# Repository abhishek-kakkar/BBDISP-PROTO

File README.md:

This is a display cape for the BeagleBone Black using a readily available tablet screen and touch panel.

Visit [this page](https://hackaday.io/project/4410-yet-another-beaglebone-displaycaptouch-cape) for more information.

© 2015 Kumar Abhishek.

Licensed under the CERN Open Hardware License.

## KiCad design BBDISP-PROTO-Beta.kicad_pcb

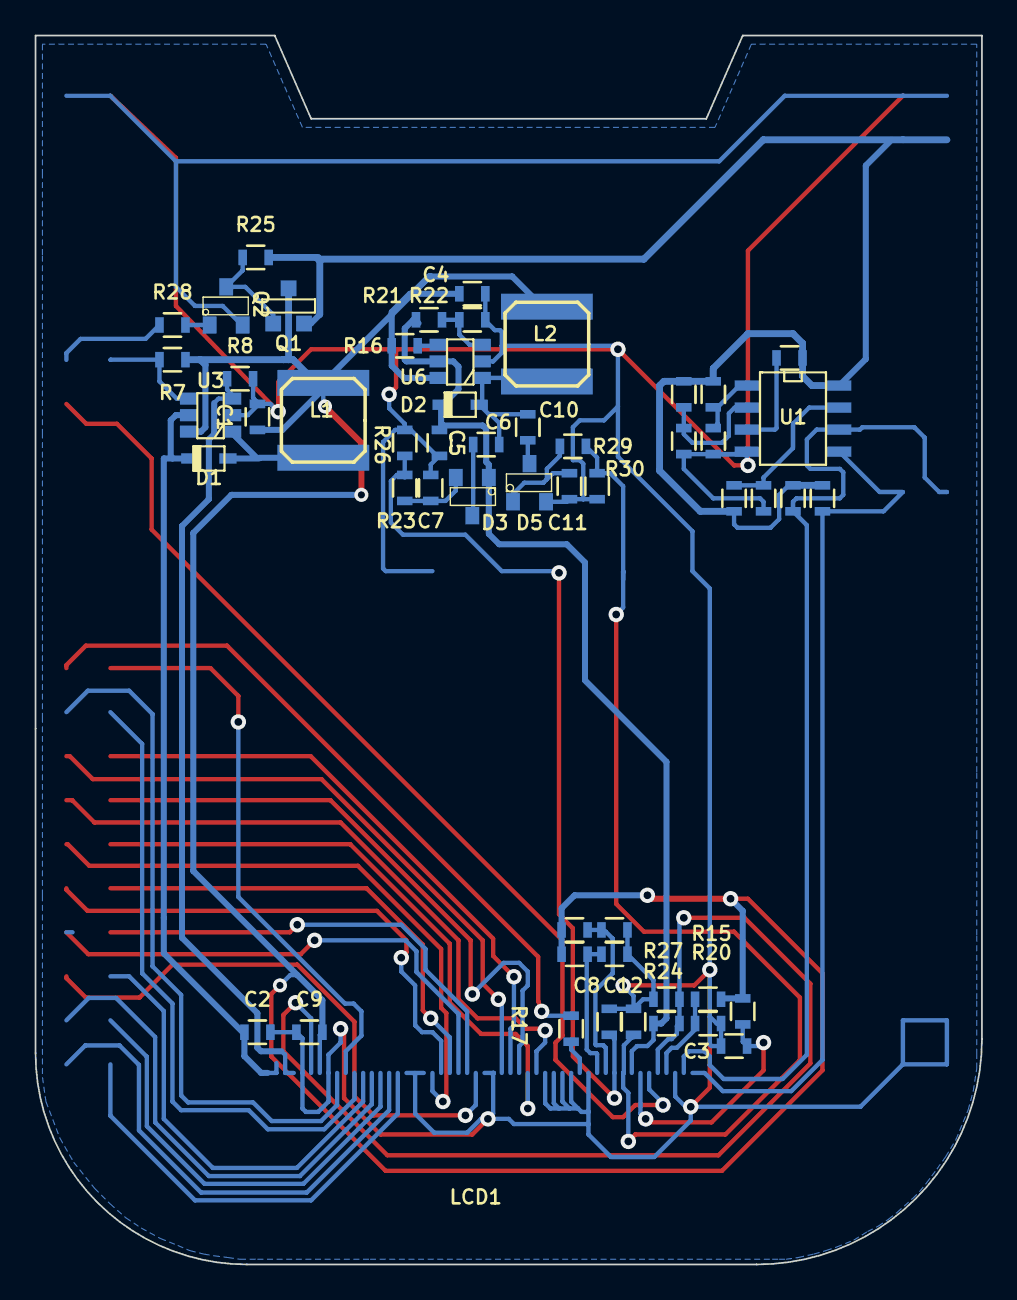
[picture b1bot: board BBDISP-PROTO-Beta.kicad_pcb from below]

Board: 2 copper layers, 54.6 x 70.9 mm, 54 parts (54 on the bottom side), 30 nets.

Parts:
C1, C2, C4, C5: 224; R_0603
C3, C6, C7, C8, C9, C10, C11, C12: 104; R_0603
D1, D2: DIODESCH; sod323
D3, D5: BAT54S; SOT-23_Inv
L1, L2: 22uH; SELF-WE-TPC_M
LCD1: Generic_7; df12a(3.0)-50ds-0.5v
Q1: AO3401; SOT-23-GDS
Q2: BC847; SOT-23
R1, R2: 4K7; R_0603
R3, R4, R5, R6, R7, R9, R10, R11, R12, R16: 10K; R_0603
R8, R13, R14, R15, R17, R18, R19, R20, R21, R22, R24, R27: TBD; R_0603
R23, R29: 1K5; R_0603
R25, R28: 100K; R_0603
R26, R30: 47K; R_0603
U1: AT24CS64-SSHM; SOIC-8-W
U3, U6: SY7201ABC; SOT-23-6

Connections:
+3V3: Q1.S, R1.2, R2.2, R3.2, R4.2, R5.2, R6.2, R25.2, U1.8
+3V3_B: C1.1, C4.1, C9.2, L1.1, L2.1, Q1.D, R7.1, R12.2, R13.1, R14.1, R15.1, R16.1, U3.6, U6.6
/AVDD: C5.1, D2.2, D3.1, R21.1, R24.1, U6.5
/BL_PWM: R7.2, U3.4
/I2C2_SCL: R1.1, U1.6
/I2C2_SDA: R2.1, U1.5
/LCD_DITHB: R15.2, R20.1
/LCD_LR: R13.2, R18.1
/LCD_UD: R14.2, R19.1
/SW1: D1.1, L1.2, U3.1
/SW2: C6.2, C10.2, D2.1, L2.2, U6.1
/VCOM: R24.2, R27.1
/VGH: C8.2, R23.1, R26.2
/VGL: C12.2, R29.1, R30.2
/VLED: C2.1, D1.2, U3.5
GND: C1.2, C2.2, C3.1, C4.2, C5.2, C7.1, C8.1, C9.1, C11.1, C12.1, D5.3, Q2.2, R8.2, R9.1, R10.1, R11.1, R18.2, R19.2, R20.2, R22.2, R26.1, R27.2, R30.1, U1.4, U3.2, U6.2
unnamed: C3.2, R12.1
unnamed: C6.1, D3.2
unnamed: C7.2, D3.3, R23.2
unnamed: C10.1, D5.2
unnamed: C11.2, D5.1, R29.2
unnamed: R8.1, U3.3
unnamed: Q1.G, Q2.3, R25.1
unnamed: Q2.1, R28.2
unnamed: R3.1, R9.2, U1.7
unnamed: R4.1, U1.3
unnamed: R5.1, R10.2, U1.2
unnamed: R6.1, R11.2, U1.1
unnamed: R16.2, U6.4
unnamed: R21.2, R22.1, U6.3

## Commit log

2015-05-27 Add README.md
2015-05-27 Add cape design files
2015-05-27 Add adapter board files
